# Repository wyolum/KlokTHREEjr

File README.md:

# KlokTHREEjr
RGB LED matrix for text and animation display.

License
-------
[CERN Open Hardware Licence v1.2 ]

[CERN Open Hardware Licence v1.2 ]:http://www.ohwr.org/attachments/2388/cern_ohl_v_1_2.txt

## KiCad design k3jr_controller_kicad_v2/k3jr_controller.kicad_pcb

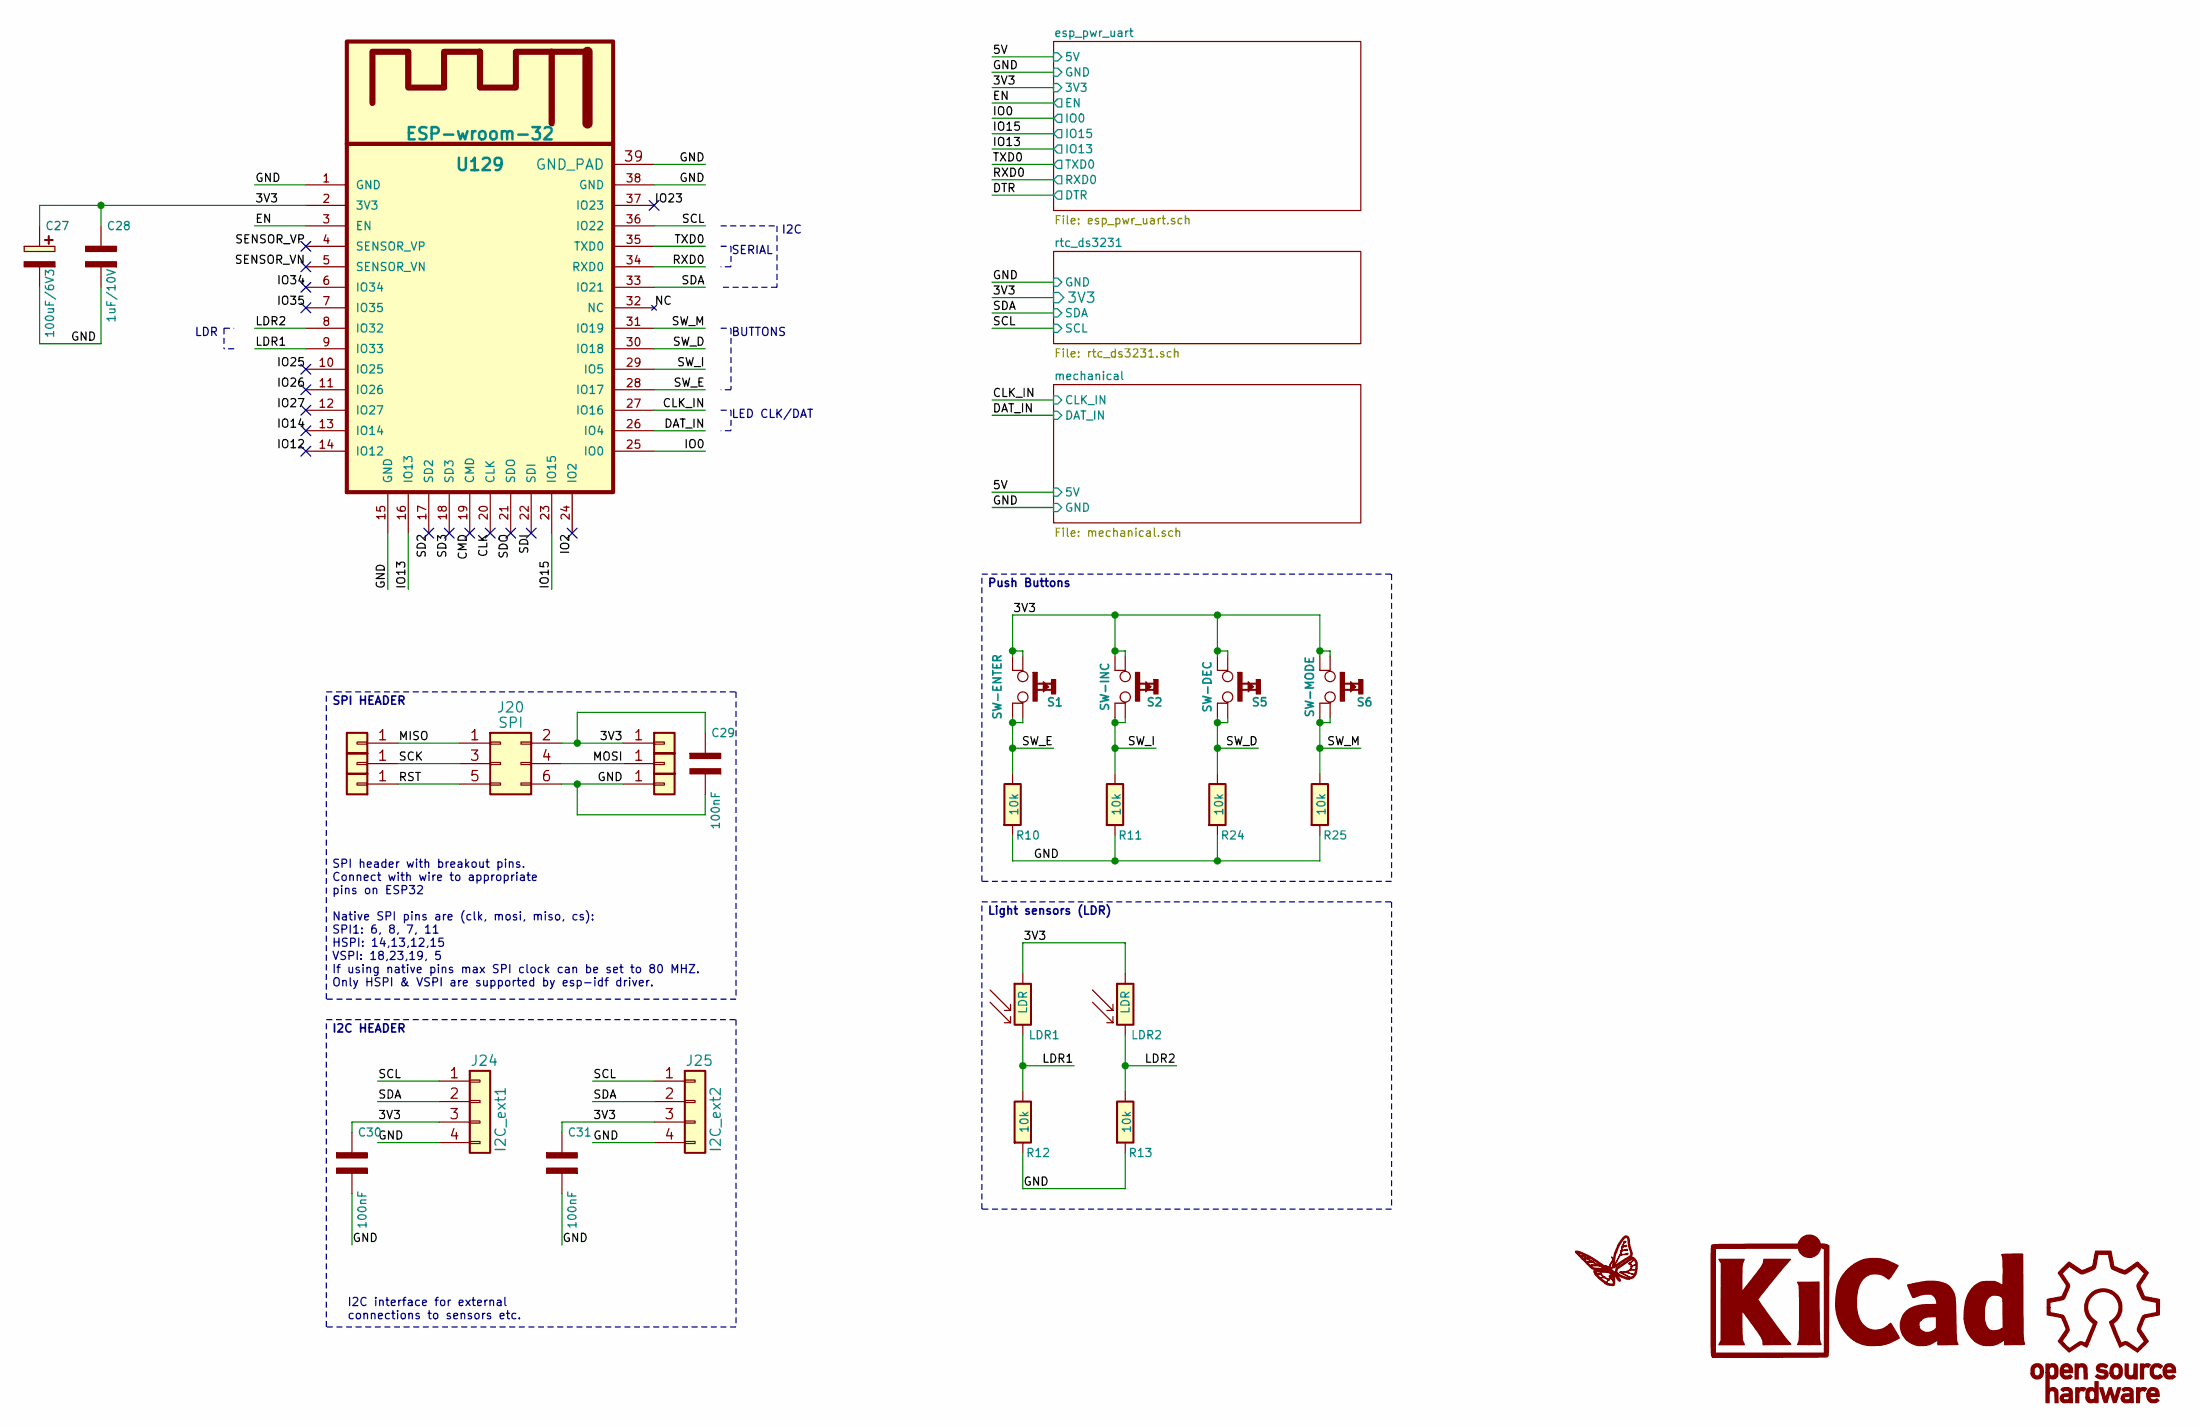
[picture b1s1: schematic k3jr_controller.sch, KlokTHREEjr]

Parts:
C27: 100uF/6V3; c_2917
C28: 1uF/10V; c_0805
C29, C30, C31: 100nF; c_0805
G1: LOGO_WL; Logo-WL3
G2: KiCad; KiCad-Logo2_6mm_SilkScreen
G3: OSHW; OSHW_6mm
J17: MISO; BreakOutPad
J18: 3V3; BreakOutPad
J19: SCK; BreakOutPad
J20: SPI; Header_ISP
J21: MOSI; BreakOutPad
J22: RST; BreakOutPad
J23: GND; BreakOutPad
J24: I2C_ext1; Header_4x1
J25: I2C_ext2; Header_4x1
LDR1, LDR2: LDR; r_0805_ldr_2
R10, R11, R12, R13, R24, R25: 10k; r_0805
S1: SW-ENTER; SW_SMD
S2: SW-INC; SW_SMD
S5: SW-DEC; SW_SMD
S6: SW-MODE; SW_SMD
U129: ESP-wroom-32; esp_wroom_32

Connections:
/3V3: C27.1 (+), C28.1 (+), C29.1 (+), C30.1 (+), C31.1 (+), J18.1, J20.2, J24.3, J25.3, LDR1.1, LDR2.1, S1.1, S1.3, S2.1, S2.3, S5.1, S5.3, S6.1, S6.3, U129.2 (3V3); also elsewhere on the board
/CLK: U129.20 (CLK)
/CLK_IN: U129.27 (IO16); also elsewhere on the board
/CMD: U129.19 (CMD)
/DAT_IN: U129.26 (IO4); also elsewhere on the board
/EN: U129.3 (EN); also elsewhere on the board
/IO0: U129.25 (IO0); also elsewhere on the board
/IO2: U129.24 (IO2)
/IO12: U129.14 (IO12)
/IO13: U129.16 (IO13); also elsewhere on the board
/IO14: U129.13 (IO14)
/IO15: U129.23 (IO15); also elsewhere on the board
/IO23: U129.37 (IO23)
/IO25: U129.10 (IO25)
/IO26: U129.11 (IO26)
/IO27: U129.12 (IO27)
/IO34: U129.6 (IO34)
/IO35: U129.7 (IO35)
/LDR1: LDR1.2, R12.1, U129.9 (IO33)
/LDR2: LDR2.2, R13.1, U129.8 (IO32)
/MISO: J17.1, J20.1
/MOSI: J20.4, J21.1
/NC: U129.32 (NC)
/RST: J20.5, J22.1
/RXD0: U129.34 (RXD0); also elsewhere on the board
/SCK: J19.1, J20.3
/SCL: J24.1, J25.1, U129.36 (IO22); also elsewhere on the board
/SD2: U129.17 (SD2)
/SD3: U129.18 (SD3)
/SDA: J24.2, J25.2, U129.33 (IO21); also elsewhere on the board
/SDI: U129.22 (SDI)
/SDO: U129.21 (SDO)
/SENSOR_VN: U129.5 (SENSOR_VN)
/SENSOR_VP: U129.4 (SENSOR_VP)
/SW_D: R24.1, S5.2, S5.4, U129.30 (IO18)
/SW_E: R10.1, S1.2, S1.4, U129.28 (IO17)
/SW_I: R11.1, S2.2, S2.4, U129.29 (IO5)
/SW_M: R25.1, S6.2, S6.4, U129.31 (IO19)
/TXD0: U129.35 (TXD0); also elsewhere on the board
GND: C27.2 (-), C28.2 (-), C29.2 (-), C30.2 (-), C31.2 (-), J20.6, J23.1, J24.4, J25.4, R10.2, R11.2, R12.2, R13.2, R24.2, R25.2, U129.1 (GND), U129.15 (GND), U129.38 (GND), U129.39 (GND_PAD); also elsewhere on the board

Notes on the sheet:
Push Buttons
Light sensors (LDR)
BUTTONS
LED CLK/DAT
I2C
SERIAL
LDR
Native SPI pins are (clk, mosi, miso, cs): SPI1: 6, 8, 7, 11 HSPI: 14,13,12,15 VSPI: 18,23,19, 5 If using native pins max SPI clock can be set to 80 MHZ. Only HSPI & VSPI are supported by esp-idf driver.
SPI header with breakout pins. Connect with wire to appropriate pins on ESP32
I2C interface for external connections to sensors etc.
SPI HEADER
I2C HEADER

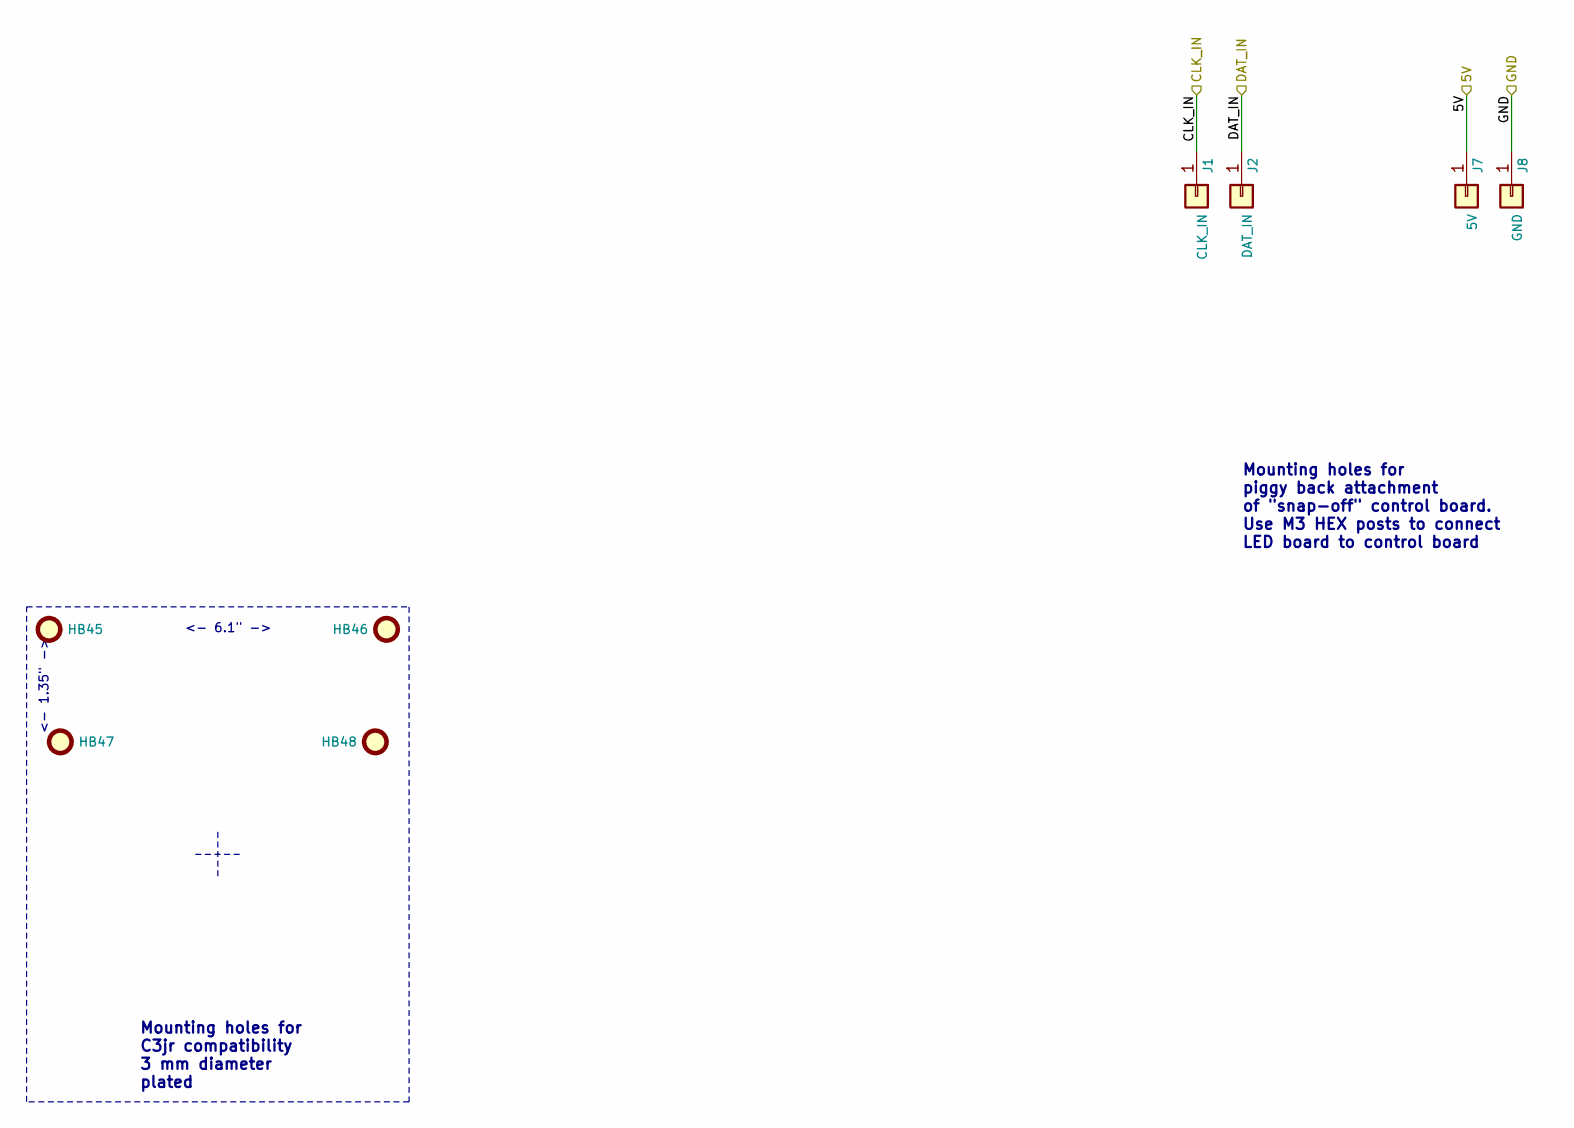
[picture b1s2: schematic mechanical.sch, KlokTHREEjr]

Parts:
HB45, HB46: mtg_hole_3mm_small; MountingHole_3.2mm_M3
HB47, HB48: mtg_hole_3mm; MountingHole_3.2mm_M3_Pad_Via
J1: CLK_IN; 1pin
J2: DAT_IN; 1pin
J7: 5V; 1pin
J8: GND; 1pin

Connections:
/5V: J7.1; also elsewhere on the board
/CLK_IN: J1.1; also elsewhere on the board
/DAT_IN: J2.1; also elsewhere on the board
GND: J8.1; also elsewhere on the board

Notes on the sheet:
<- 6.1" ->
<- 1.35" ->
Mounting holes for C3jr compatibility 3 mm diameter plated
Mounting holes for piggy back attachment of "snap-off" control board. Use M3 HEX posts to connect LED board to control board

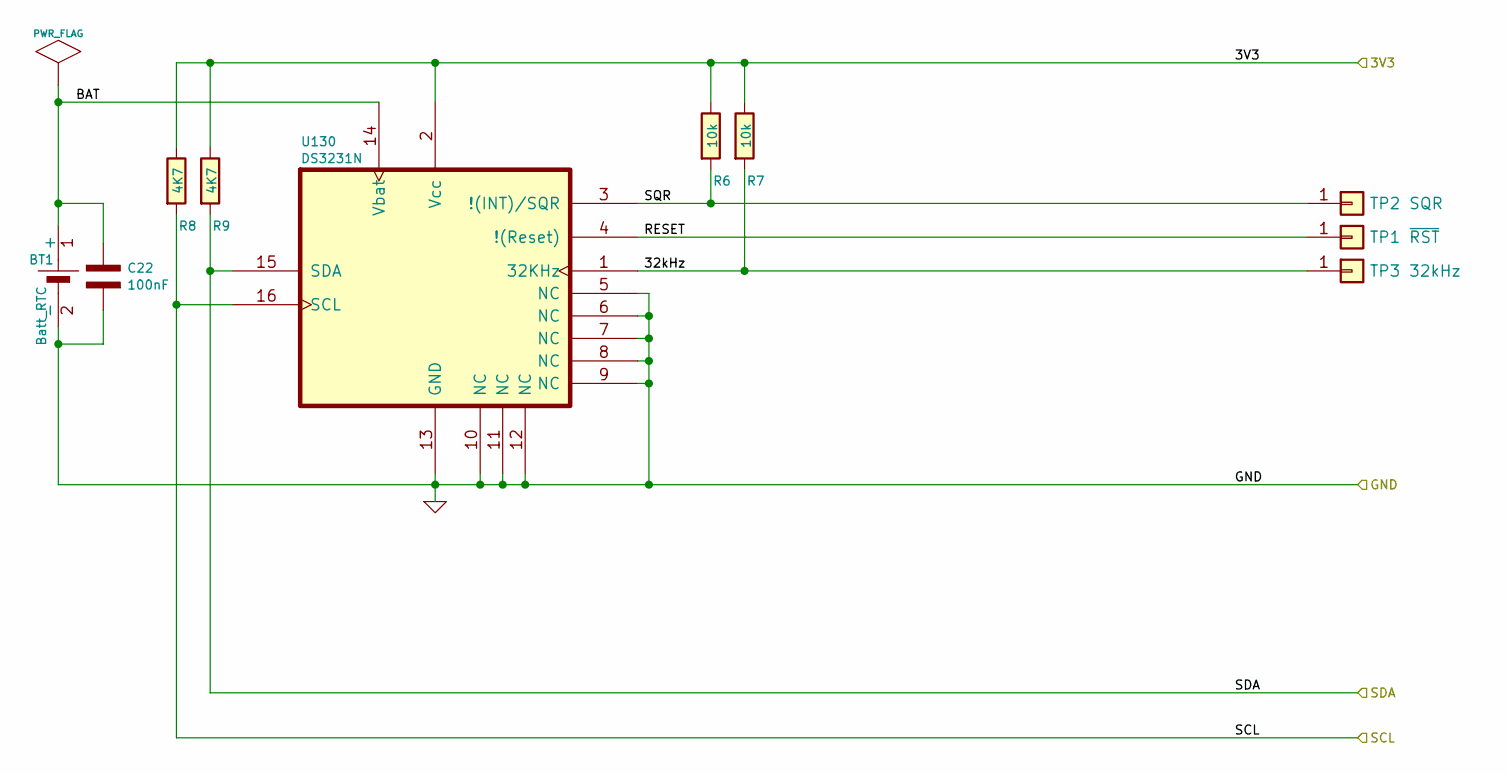
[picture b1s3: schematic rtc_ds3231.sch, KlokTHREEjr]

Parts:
BT1: Batt_RTC; CR2032_SMD2; Digikey BU2032SM-HD-GCT-ND
C22: 100nF; c_0805
R6, R7: 10k; r_0805
R8, R9: 4K7; r_0805
TP1: ~RST; BreakOutPad
TP2: SQR; BreakOutPad
TP3: 32kHz; BreakOutPad
U130: DS3231N; DS3231

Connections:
/3V3: R6.1, R7.1, R8.1, R9.1, U130.2 (Vcc); also elsewhere on the board
/SCL: R8.2, U130.16 (SCL); also elsewhere on the board
/SDA: R9.2, U130.15 (SDA); also elsewhere on the board
/rtc_ds3231/32kHz: R7.2, TP3.1, U130.1 (32KHz)
/rtc_ds3231/BAT: BT1.1 (+), C22.1 (+), U130.14 (Vbat)
/rtc_ds3231/RESET: TP1.1, U130.4 (!(Reset))
/rtc_ds3231/SQR: R6.2, TP2.1, U130.3 (!(INT)/SQR)
GND: BT1.2 (-), C22.2 (-), U130.5 (NC), U130.6 (NC), U130.7 (NC), U130.8 (NC), U130.9 (NC), U130.10 (NC), U130.11 (NC), U130.12 (NC), U130.13 (GND); also elsewhere on the board

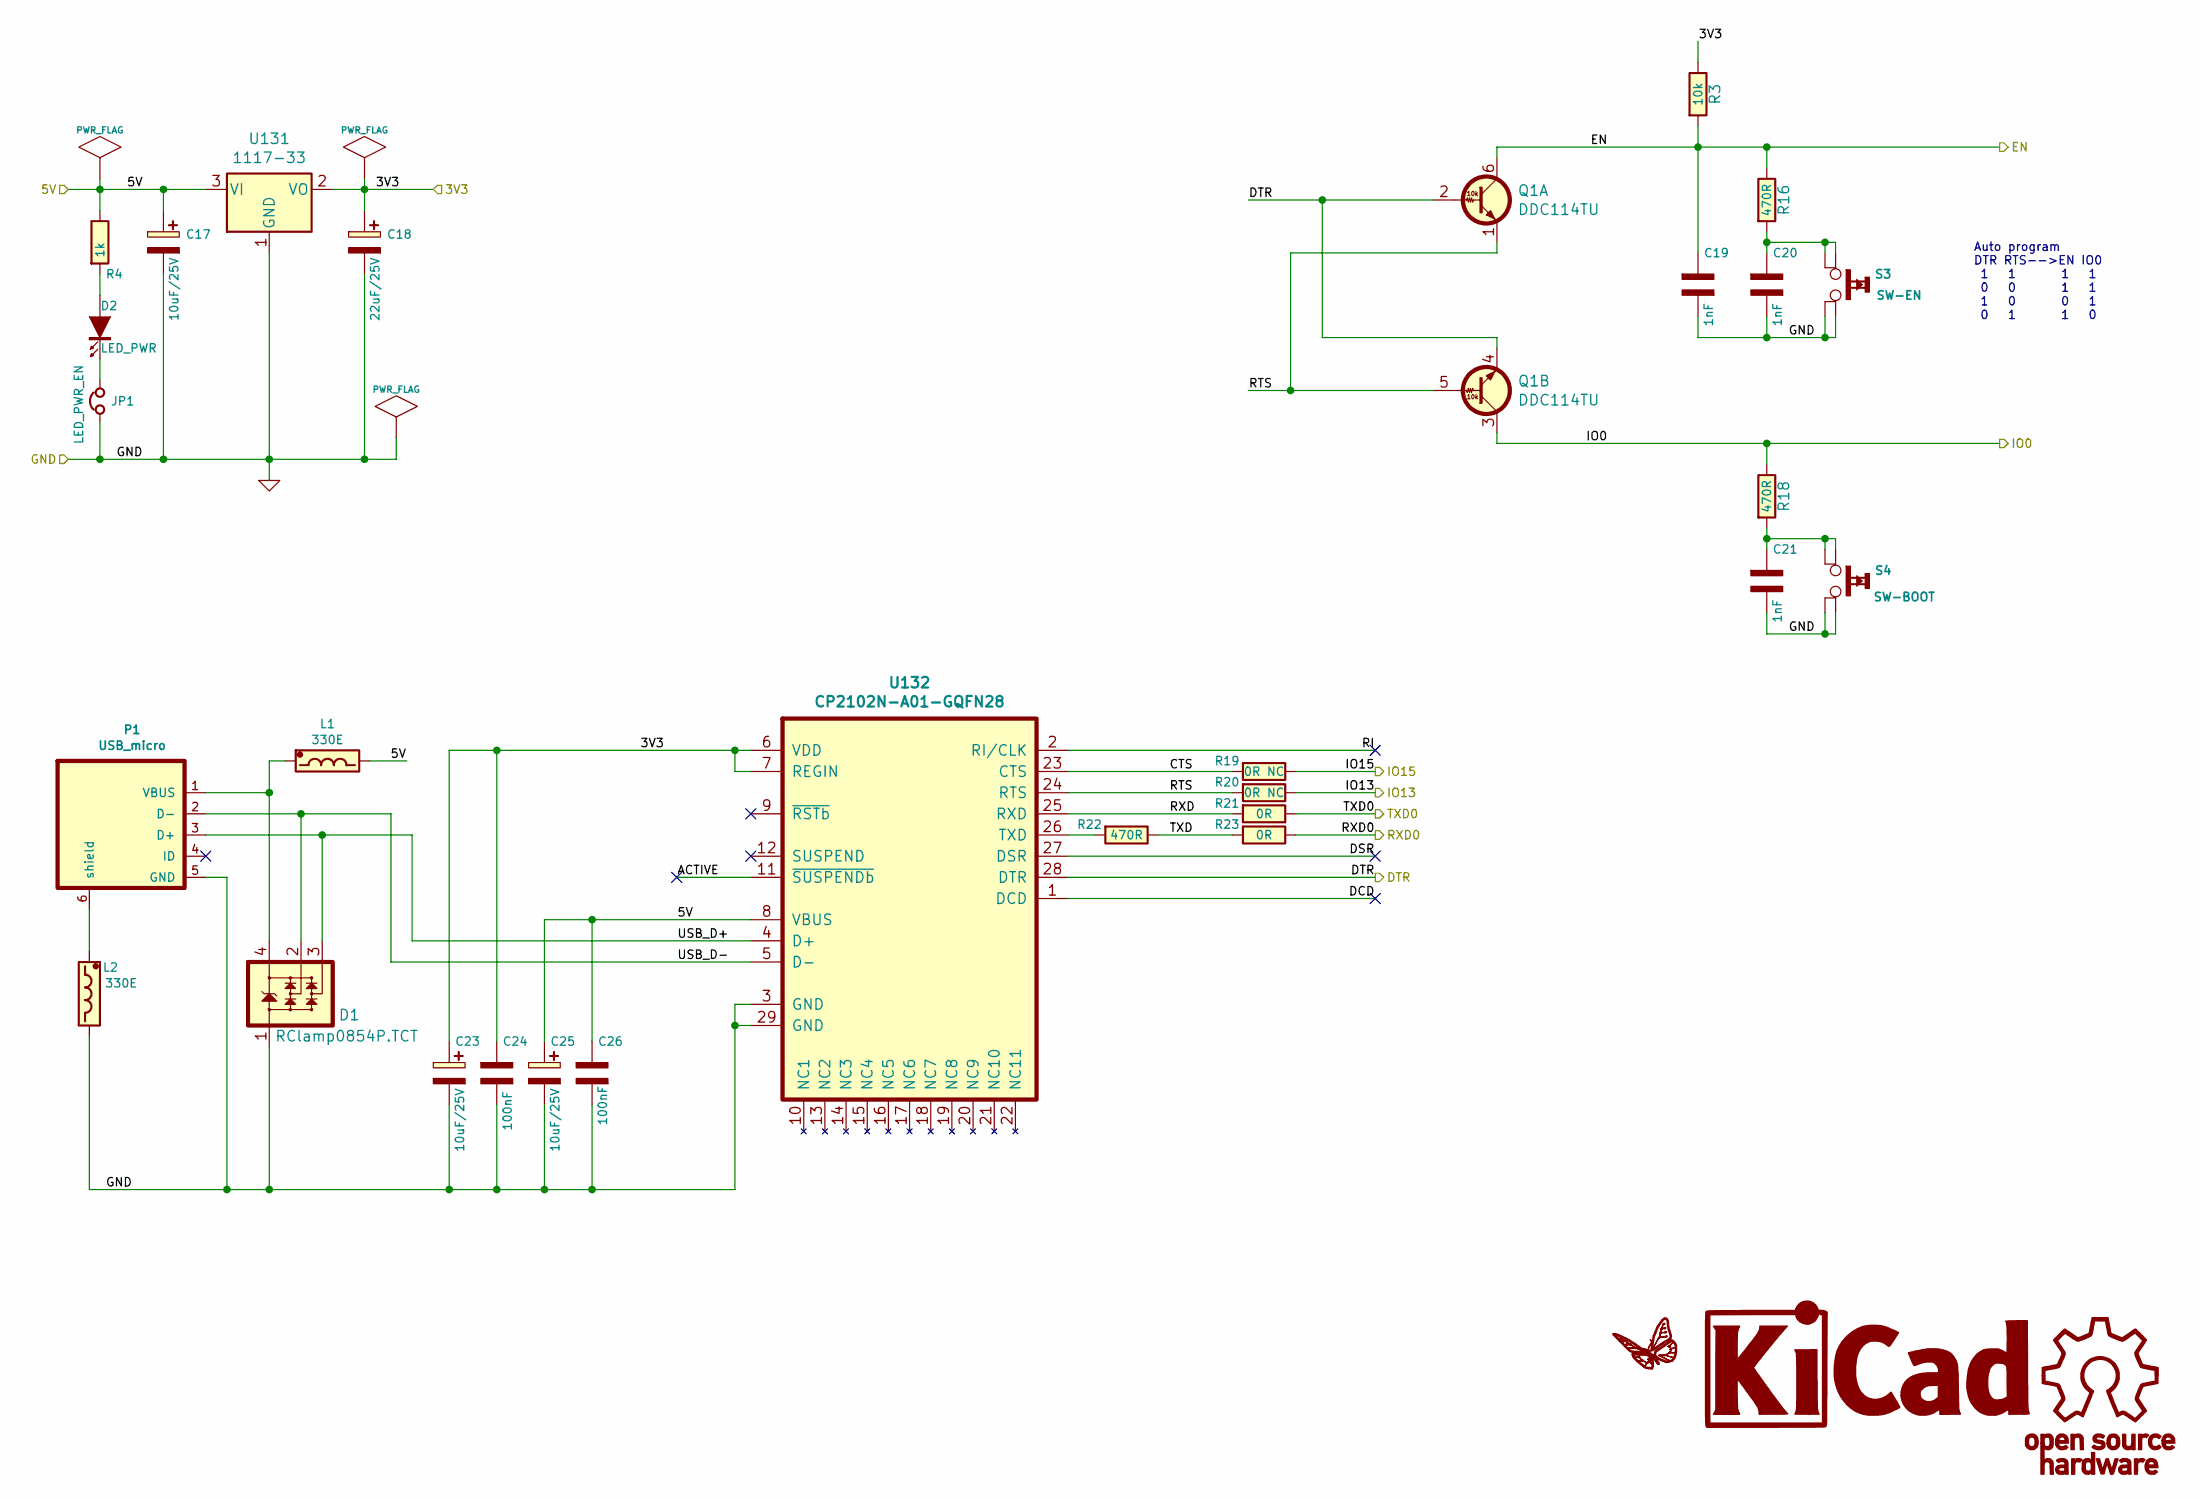
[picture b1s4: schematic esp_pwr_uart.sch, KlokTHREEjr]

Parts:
C17, C23, C25: 10uF/25V; c_2917
C18: 22uF/25V; c_2917
C19, C20, C21: 1nF; c_0805
C24, C26: 100nF; c_0805
D1: RClamp0854P.TCT; SOT-143
D2: LED_PWR; LED-0805
G7: LOGO_WL; Logo-WL3
G8: KiCad; KiCad-Logo2_6mm_SilkScreen
G9: OSHW; OSHW_6mm
JP1: LED_PWR_EN; R_0402
L1, L2: 330E; r_0805
P1: USB_micro; USB_Micro-B_Molex-105017-0001
Q1: DDC114TU; SOT-363_SC-70-6
R3: 10k; r_0805
R4: 1k; r_0805
R16, R18, R22: 470R; r_0805
R19, R20: 0R NC; r_0805
R21, R23: 0R; r_0805
S3: SW-EN; SW_SMD
S4: SW-BOOT; SW_SMD
U131: 1117-33; SOT-223-3_TabPin2
U132: CP2102N-A01-GQFN28; QFN-28-1EP_5x5mm_Pitch0.5mm

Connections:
/3V3: C18.1 (+), C23.1 (+), C24.1 (+), R3.1, U131.2 (VO), U132.6 (VDD), U132.7 (REGIN); also elsewhere on the board
/5V: C17.1 (+), C25.1 (+), C26.1 (+), L1.2, R4.1, U131.3 (VI), U132.8 (VBUS); also elsewhere on the board
/DTR: Q1.2 (B1), Q1.4 (E2), U132.28 (DTR)
/EN: C19.1 (+), Q1.6 (C1), R3.2, R16.1; also elsewhere on the board
/IO0: Q1.3 (C2), R18.1; also elsewhere on the board
/IO13: R20.1; also elsewhere on the board
/IO15: R19.1; also elsewhere on the board
/RXD0: R23.1; also elsewhere on the board
/TXD0: R21.1; also elsewhere on the board
/esp_pwr_uart/ACTIVE: U132.11 (~SUSPENDb)
/esp_pwr_uart/CTS: R19.2, U132.23 (CTS)
/esp_pwr_uart/DCD: U132.1 (DCD)
/esp_pwr_uart/DSR: U132.27 (DSR)
/esp_pwr_uart/RI: U132.2 (RI/CLK)
/esp_pwr_uart/RTS: Q1.1 (E1), Q1.5 (B2), R20.2, U132.24 (RTS)
/esp_pwr_uart/RXD: R21.2, U132.25 (RXD)
/esp_pwr_uart/TXD: R22.1, R23.2
/esp_pwr_uart/USB_D+: D1.3, P1.3 (D+), U132.4 (D+)
/esp_pwr_uart/USB_D-: D1.2, P1.2 (D-), U132.5 (D-)
GND: C17.2 (-), C18.2 (-), C19.2 (-), C20.2 (-), C21.2 (-), C23.2 (-), C24.2 (-), C25.2 (-), C26.2 (-), D1.1, JP1.1, L2.2, P1.5 (GND), S3.2, S3.4, S4.2, S4.4, U131.1 (GND), U132.3 (GND), U132.29 (GND); also elsewhere on the board
unnamed: C20.1 (+), R16.2, S3.1, S3.3
unnamed: C21.1 (+), R18.2, S4.1, S4.3
unnamed: D1.4, L1.1, P1.1 (VBUS)
unnamed: D2.1 (A), R4.2
unnamed: D2.2 (K), JP1.2
unnamed: L2.1, P1.6 (shield)
unnamed: R22.2, U132.26 (TXD)

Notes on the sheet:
Auto program DTR RTS-->EN IO0 1 1 1 1 0 0 1 1 1 0 0 1 0 1 1 0

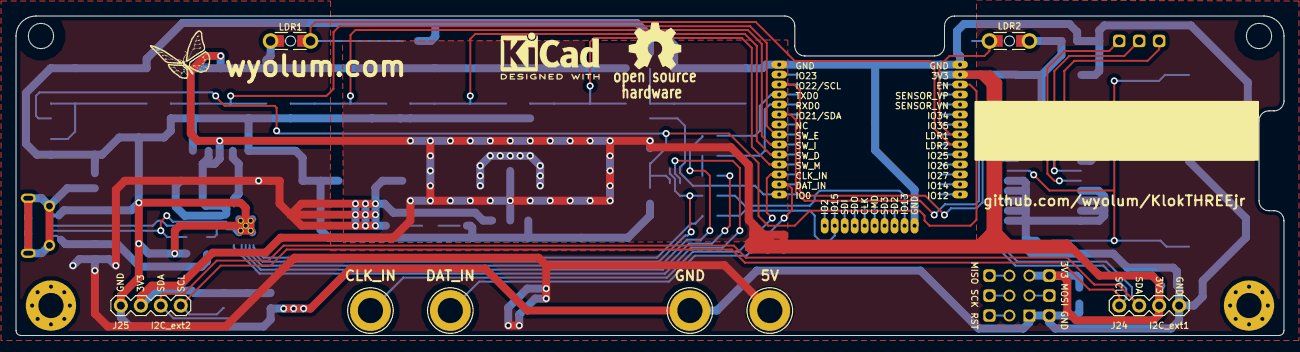
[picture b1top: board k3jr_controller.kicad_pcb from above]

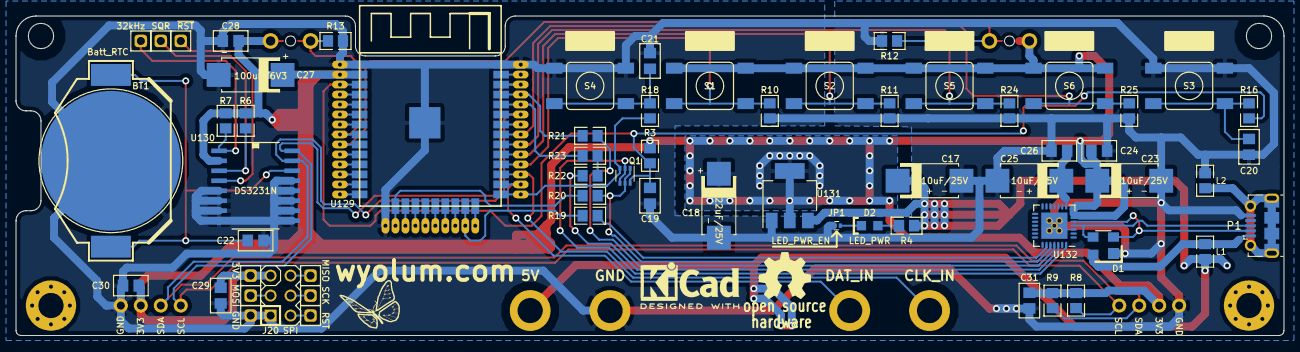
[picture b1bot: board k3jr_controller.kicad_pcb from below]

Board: 2 copper layers, 161.3 x 40.6 mm, 80 parts (65 on the bottom side), 41 nets.

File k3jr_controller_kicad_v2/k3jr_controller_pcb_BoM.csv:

"Id";"Designator";"Package";"Quantity";"Designation";"Supplier and ref";
1;"BT1";"CR2032_SMD2";1;"Batt_RTC";;;
2;"LDR1,LDR2";"r_0805_ldr_2";2;"LDR";;;
3;"S5";"SW_SMD";1;"SW-DEC";;;
4;"C17,C25,C23";"c_2917";3;"10uF/25V";;;
5;"D1";"SOT-143";1;"RClamp0854P.TCT";;;
6;"P1";"USB_Micro-B_Molex-105017-0001";1;"USB_micro";;;
7;"HB47,HB48";"MountingHole_3.2mm_M3_Pad_Via";2;"mtg_hole_3mm";;;
8;"S6";"SW_SMD";1;"SW-MODE";;;
9;"C27";"c_2917";1;"100uF/6V3";;;
10;"U132";"QFN-28-1EP_5x5mm_Pitch0.5mm";1;"CP2102N-A01-GQFN28";;;
11;"R25,R24,R11,R10,R3,R7,R6,R12,R13";"r_0805";9;"10k";;;
12;"C31,C22,C26,C24,C29,C30";"c_0805";6;"100nF";;;
13;"S4";"SW_SMD";1;"SW-BOOT";;;
14;"HB45,HB46";"MountingHole_3.2mm_M3";2;"mtg_hole_3mm_small";;;
15;"G1,G7";"Logo-WL3";2;"LOGO_WL";;;
16;"C18";"c_2917";1;"22uF/25V";;;
17;"R9,R8";"r_0805";2;"4K7";;;
18;"U131";"SOT-223-3_TabPin2";1;"1117-33";;;
19;"R23,R21";"r_0805";2;"0R";;;
20;"R22,R18,R16";"r_0805";3;"470R";;;
21;"R20,R19";"r_0805";2;"0R NC";;;
22;"R4";"r_0805";1;"1k";;;
23;"Q1";"SOT-363_SC-70-6";1;"DDC114TU";;;
24;"C28";"c_0805";1;"1uF/10V";;;
25;"C21,C20,C19";"c_0805";3;"1nF";;;
26;"TP1";"BreakOutPad";1;"~RST";;;
27;"S2";"SW_SMD";1;"SW-INC";;;
28;"U130";"DS3231";1;"DS3231N";;;
29;"S3";"SW_SMD";1;"SW-EN";;;
30;"J8";"1pin";1;"GND";;;
31;"J7";"1pin";1;"5V";;;
32;"J23";"BreakOutPad";1;"GND";;;
33;"J22";"BreakOutPad";1;"RST";;;
34;"J21";"BreakOutPad";1;"MOSI";;;
35;"J20";"Header_ISP";1;"SPI";;;
36;"J19";"BreakOutPad";1;"SCK";;;
37;"J18";"BreakOutPad";1;"3V3";;;
38;"J17";"BreakOutPad";1;"MISO";;;
39;"TP3";"BreakOutPad";1;"32kHz";;;
40;"TP2";"BreakOutPad";1;"SQR";;;
41;"J25";"Header_4x1";1;"I2C_ext2";;;
42;"J24";"Header_4x1";1;"I2C_ext1";;;
43;"G3,G9";"OSHW_6mm";2;"OSHW";;;
44;"G2,G8";"KiCad-Logo2_6mm_SilkScreen";2;"KiCad";;;
45;"J2";"1pin";1;"DAT_IN";;;
46;"J1";"1pin";1;"CLK_IN";;;
47;"JP1";"R_0402";1;"LED_PWR_EN";;;
48;"U129";"esp_wroom_32";1;"ESP-wroom-32";;;
49;"S1";"SW_SMD";1;"SW-ENTER";;;
50;"D2";"LED-0805";1;"LED_PWR";;;
51;"L1,L2";"r_0805";2;"330E";;;
